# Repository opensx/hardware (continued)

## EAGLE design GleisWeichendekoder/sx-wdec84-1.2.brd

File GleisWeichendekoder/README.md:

# Weichendekoder für den direkten Anschluss ans Gleis 

Dies ist ein Weichendekoder zum direkten Einbau z.B. in das "C-Gleis", mehr dazu bei <a href="http://opensx.net/projekte/funktionsdekoder/gleis-wdec/"> Gleis-Weichendekoder auf opensx.net</a> .

<br />This work is licensed under a <a rel="license" href="http://creativecommons.org/licenses/by-sa/4.0/">Creative Commons Attribution-ShareAlike 4.0 International License</a>.

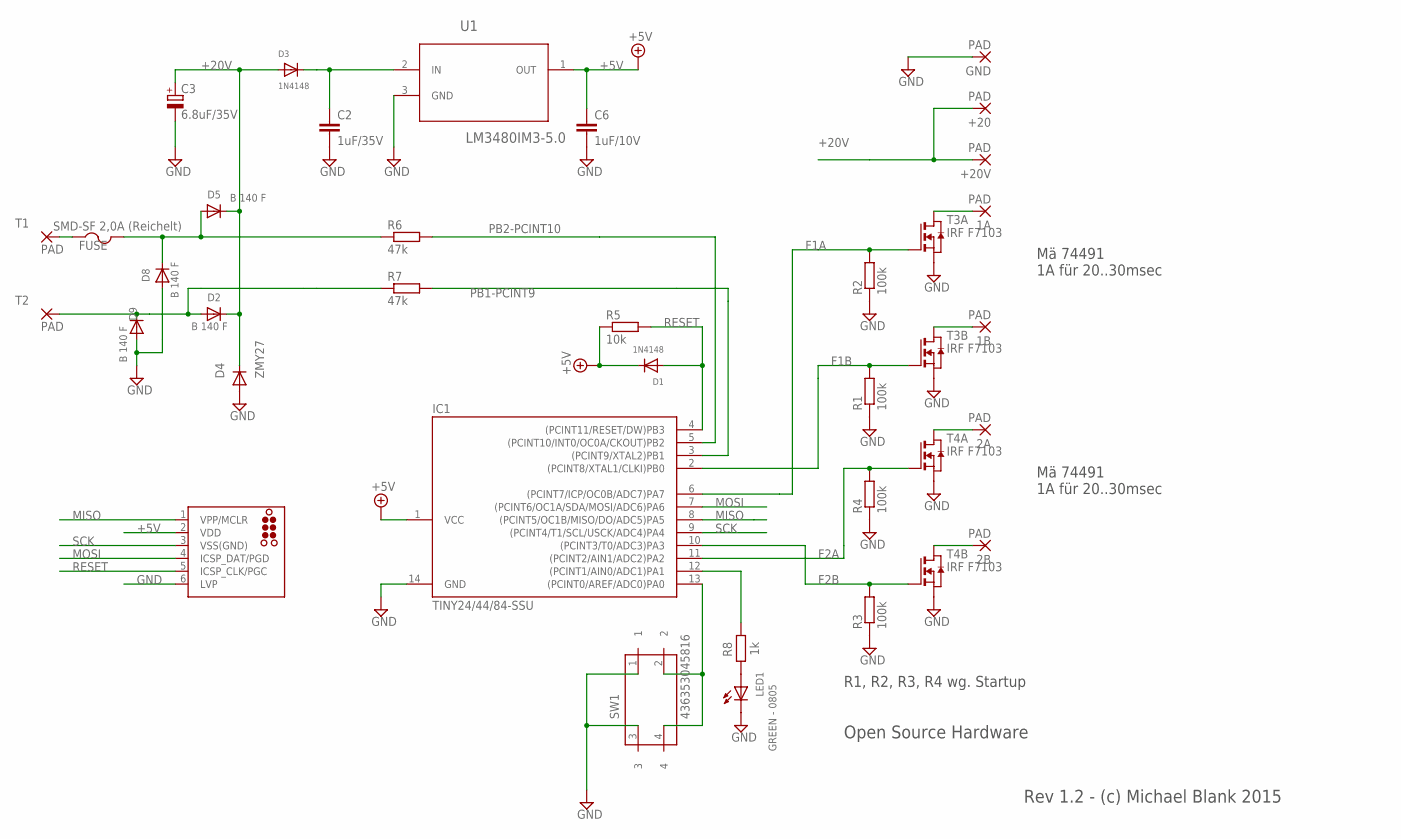
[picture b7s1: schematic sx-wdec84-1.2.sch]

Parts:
1A, 1B, 2A, 2B: PAD; SMD1,27-2,54
+20, +20V: PAD; SMD1,27-2,54
C2: 1uF/35V; C0805
C3: 6.8uF/35V; SMC_D
C6: 1uF/10V; C0805
D1, D3: 1N4148; SOD-323F
D2, D5, D8, D9: B 140 F; SMA-403D
D4: ZMY27; MELF-MLL41
FUSE: SMD-SF 2,0A (Reichelt); 1812
GND: PAD; SMD1,27-2,54
IC1: TINY24/44/84-SSU; SOIC14
J1: ISP; TC2030-MCP-NL
LED1: GREEN - 0805; LED-0805
R1, R2, R3, R4: 100k; R0805W
R5: 10k; R0805W
R6, R7: 47k; R0805W
R8: 1k; R0805W
SW1: 436353045816
T1, T2: PAD; SMD1,27-2,54
T3, T4: IRF F7103; SO8
U1: LM3480IM3-5.0; SOT95P263X110-3N

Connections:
+5V: C6.1, D1.C, IC1.1 (VCC), J1.2 (VDD), R5.1, U1.1 (OUT)
+20V: +20.1, +20V.1, C3.+, D2.C, D3.A, D4.C, D5.C
F1A: IC1.6 ((PCINT7/ICP/OC0B/ADC7)PA7), R2.2, T3.2 (G)
F1B: IC1.2 ((PCINT8/XTAL1/CLKI)PB0), R1.2, T3.4 (G)
F2A: IC1.11 ((PCINT2/AIN1/ADC2)PA2), R4.2, T4.2 (G)
F2B: IC1.10 ((PCINT3/T0/ADC3)PA3), R3.2, T4.4 (G)
GND: C2.2, C3.-, C6.2, D4.A, D8.A, D9.A, GND.1, IC1.14 (GND), J1.6 (LVP), LED1.C, R1.1, R2.1, R3.1, R4.1, SW1.1, SW1.3, T3.1 (S), T3.3 (S), T4.1 (S), T4.3 (S), U1.3 (GND)
MISO: IC1.8 ((PCINT5/OC1B/MISO/DO/ADC5)PA5), J1.1 (VPP/MCLR)
MOSI: IC1.7 ((PCINT6/OC1A/SDA/MOSI/ADC6)PA6), J1.4 (ICSP_DAT/PGD)
unnamed: 2B.1, T4.5 (D), T4.6 (D)
unnamed: 2A.1, T4.7 (D), T4.8 (D)
unnamed: FUSE.1, T1.1
unnamed: IC1.13 ((PCINT0/AREF/ADC0)PA0), SW1.2, SW1.4
unnamed: D5.A, D8.C, FUSE.2, R6.1
unnamed: C2.1, D3.C, U1.2 (IN)
unnamed: 1B.1, T3.5 (D), T3.6 (D)
unnamed: LED1.A, R8.2
unnamed: 1A.1, T3.7 (D), T3.8 (D)
unnamed: IC1.12 ((PCINT1/AIN0/ADC1)PA1), R8.1
PB1-PCINT9: IC1.3 ((PCINT9/XTAL2)PB1), R7.2
PB2-PCINT10: IC1.5 ((PCINT10/INT0/OC0A/CKOUT)PB2), R6.2
RESET: D1.A, IC1.4 ((PCINT11/RESET/DW)PB3), J1.5 (ICSP_CLK/PGC), R5.2
SCK: IC1.9 ((PCINT4/T1/SCL/USCK/ADC4)PA4), J1.3 (VSS(GND))
TR-L: D2.A, D9.C, R7.1, T2.1

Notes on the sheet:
Mä 74491 1A für 20..30msec
R1, R2, R3, R4 wg. Startup
Open Source Hardware
Rev 1.2 - (c) Michael Blank 2015

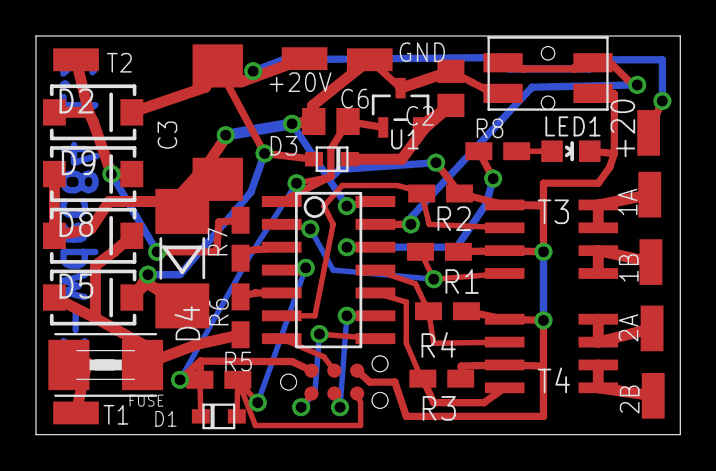
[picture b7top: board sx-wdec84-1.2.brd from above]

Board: 2 copper layers, 35.8 x 22.1 mm, 35 parts (0 on the bottom side), 24 nets.

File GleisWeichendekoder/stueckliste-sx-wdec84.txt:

Stueckliste

(sx-wdec84.brd at 13.12.15)


Part         Wert                Package            Bemerkung                Reichelt Best-Nr.

C2           1uF/35V             C0805              keram. C                 X7R-G0805 1,0/50 
C3           6.8uF/35V           SMC_D              Tantal-Elko              SMD TAN.6,8/35
C6           1uF/10V             C0805              keram. C                 X7R-G0805 1,0/16
D1, D3       1N4148              SOD-123 (falsch!)  Standard Diode           1N4148 WS
D2,D5,D8,D9  B140F               SMA-403D           Schottky-D. (40V, 1A)    B 140 F
D4           ZMY27               MELF-MLL41         Z-Diode                  SMD ZF 27
FUSE         SMD-SF 2,0A         1812               PTC                      SMD-SF 2,0A
IC1          ATTINY84-SSU        SOIC14             Atmel Proz.              ATTINY 84A-SSU
J1           ISP                 TC2030-MCP-NL                               (falls der Tiny84 in der schaltung progrmmiert 
                                                                             werden soll: TAG-CONNECT 6pin ISP)
LED1         GREEN               LED-0805                                    SMD-LED 0805 GN 
R1,R2,R3,R4  100k                R0805                                       SMD-0805 100K
R5           10k                 R0805                                       SMD-0805 100K
R6,R7        47k                 R0805                                       SMD-0805 100K
R8           1k                  R0805                                       SMD-0805 100K
S1           EVQP2202W           TACTILE_SWITCH_SMD                          (RS Components 756-1760 - oder Conrad 711761 - 62)
T3,T4        IRF F7103           SO8                Dual MosFET              IRF 7103
U1           LM3480IM3-5.0       SOT95P263X110-3N   5V Regler                (Conrad LM3480IM3-5.0/NOPB)

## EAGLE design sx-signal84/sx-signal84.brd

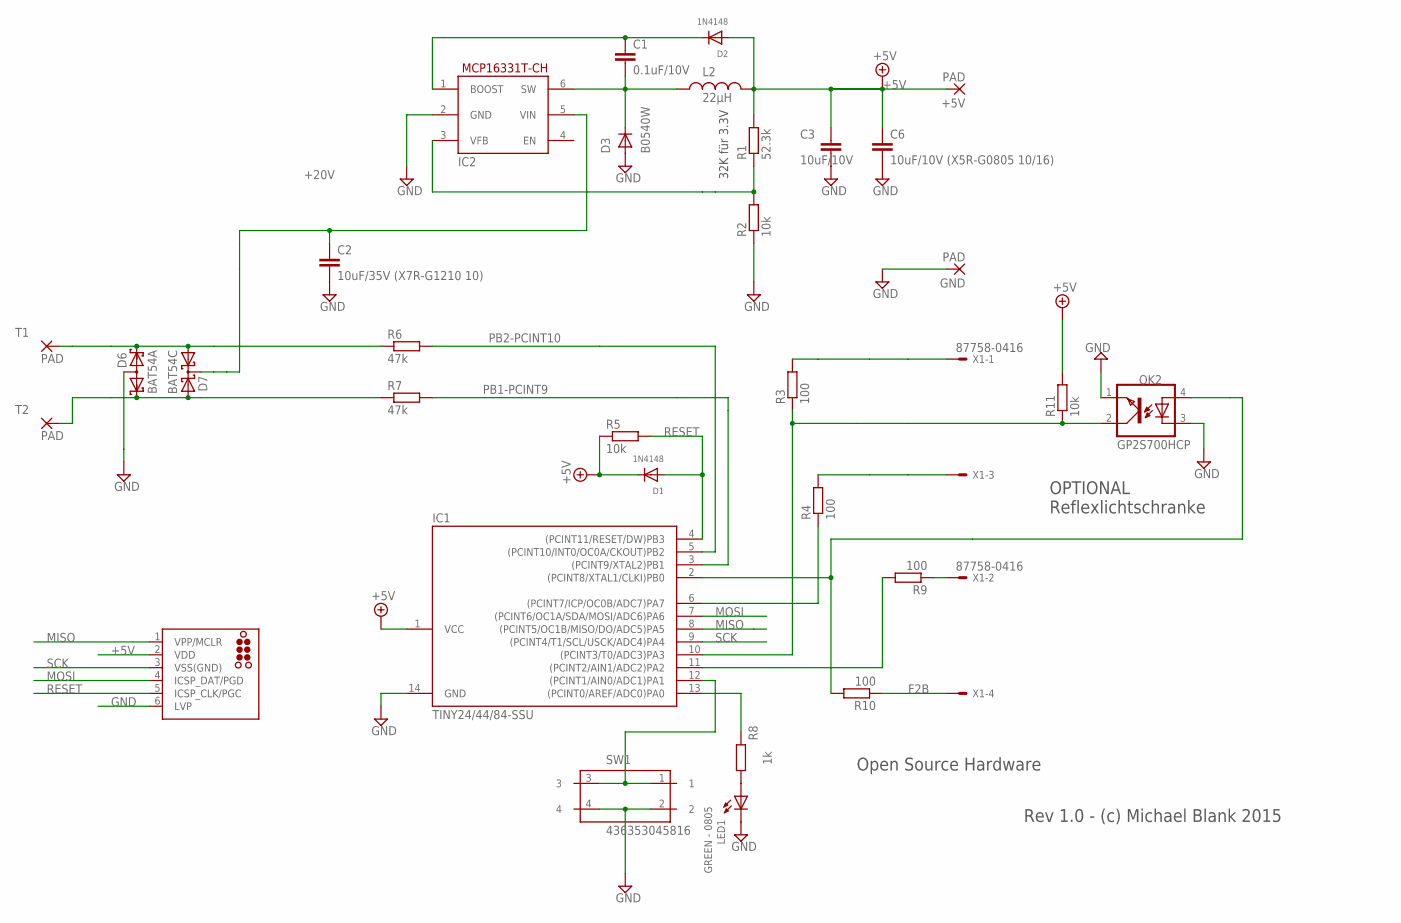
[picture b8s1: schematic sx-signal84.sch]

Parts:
+5V: PAD; SMD1,27-2,54
C1: 0.1uF/10V; C0805
C2: 10uF/35V (X7R-G1210 10); C1210
C3: 10uF/10V; C0805
C6: 10uF/10V (X5R-G0805 10/16); C0805
D1, D2: 1N4148; SOD-323F
D3: B0540W; SOD123
D6: BAT54A; SOT23
D7: BAT54C; SOT23
GND: PAD; SMD1,27-2,54
IC1: TINY24/44/84-SSU; SOIC14
IC2: MCP16331; SOT23-6
J1: ISP; TC2030-MCP-NL
L2: 22µH; B82462G
LED1: GREEN - 0805; LED-0805
OK2: GP2S700HCP; SMD4-REFL
R1: 52.3k; R0805W
R2, R5, R11: 10k; R0805W
R3, R4, R9, R10: 100; R0805W
R6, R7: 47k; R0805W
R8: 1k; R0805W
SW1: 436353045816
T1, T2: PAD; SMD1,27-2,54
X1: 87758-0416

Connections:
+5V: +5V.1, C3.1, C6.1, D1.C, D2.A, IC1.1 (VCC), J1.2 (VDD), L2.P$2 (2), R1.2, R5.1, R11.2
+20V: C2.1, D7.3 (CC), IC2.5 (VIN)
F1A: IC1.10 ((PCINT3/T0/ADC3)PA3), OK2.2 (COL), R3.1, R11.1
F1B: IC1.2 ((PCINT8/XTAL1/CLKI)PB0), OK2.4 (A), R10.2
F2B: R10.1, X1.4
GND: C2.2, C3.2, C6.2, D3.A, D6.3 (AA), GND.1, IC1.14 (GND), IC2.2 (GND), J1.6 (LVP), LED1.C, OK2.1 (EMIT), OK2.3 (C), R2.1, SW1.2, SW1.4
MISO: IC1.8 ((PCINT5/OC1B/MISO/DO/ADC5)PA5), J1.1 (VPP/MCLR)
MOSI: IC1.7 ((PCINT6/OC1A/SDA/MOSI/ADC6)PA6), J1.4 (ICSP_DAT/PGD)
unnamed: IC2.3 (VFB), R1.1, R2.2
unnamed: IC1.13 ((PCINT0/AREF/ADC0)PA0), R8.1
unnamed: IC1.12 ((PCINT1/AIN0/ADC1)PA1), SW1.1, SW1.3
unnamed: IC1.6 ((PCINT7/ICP/OC0B/ADC7)PA7), R4.1
unnamed: R9.1, X1.2
unnamed: C1.2, D3.C, IC2.6 (SW), L2.P$1 (1)
unnamed: C1.1, D2.C, IC2.1 (BOOST)
unnamed: LED1.A, R8.2
unnamed: IC1.11 ((PCINT2/AIN1/ADC2)PA2), R9.2
unnamed: D6.2 (K2), D7.1 (A1), R6.1, T1.1
unnamed: R3.2, X1.1
unnamed: R4.2, X1.3
PB1-PCINT9: IC1.3 ((PCINT9/XTAL2)PB1), R7.2
PB2-PCINT10: IC1.5 ((PCINT10/INT0/OC0A/CKOUT)PB2), R6.2
RESET: D1.A, IC1.4 ((PCINT11/RESET/DW)PB3), J1.5 (ICSP_CLK/PGC), R5.2
SCK: IC1.9 ((PCINT4/T1/SCL/USCK/ADC4)PA4), J1.3 (VSS(GND))
TR-L1: D6.1 (K1), D7.2 (A2), R7.1, T2.1

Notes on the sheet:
Open Source Hardware
Rev 1.0 - (c) Michael Blank 2015
OPTIONAL Reflexlichtschranke
32K für 3.3V

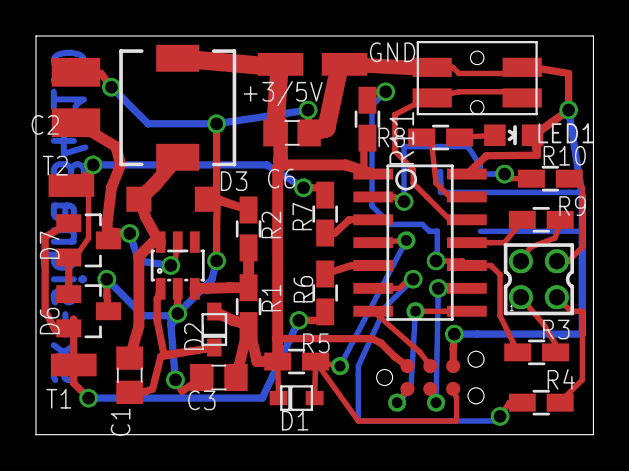
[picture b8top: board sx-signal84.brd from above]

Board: 2 copper layers, 31.0 x 22.1 mm, 32 parts (1 on the bottom side), 25 nets.

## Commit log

2015-12-13 removed cern..
2015-12-13 added linkt to cc licence
2015-12-13 Basisplatine und SX-RJ-Verteiler hinzugefügt
2015-12-13 corr readme
2015-12-13 pdf added
2015-12-13 readme corr.
2015-12-13 foto hinzu
2015-12-13 readme corr
2015-12-14 Gleis Weichendekoder hinzugefügt
2015-12-14 bild sx-wdec84 hinzu
2015-12-23 gleisdekoder hinzugefügt
2015-12-23 Gleis Signaldekoder
2016-08-26 Basisplatine-2.0 hinzugefügt
2016-08-26 fotos hinzu
2016-08-26 Belegtmelder 1.0 hinzu
2016-09-06 begin stueckliste
2016-09-16 Anleitung f. Basispl. für belegtmelder(5Volt)
2016-11-20 sx-wdec1-2313 files hinzugefügt.
2016-11-20 readme ergänzt
2016-11-20 eagle files f. sx-wdec1-2313
2016-11-20 readme korr.
2016-11-26 partlist ergänzt
2016-11-28 Create RT-Weiche-Signal
2016-11-28 neue Platine rt-weiche-signal
2016-11-28 typo README corr.
2016-12-01 RT-Weiche-Signal hardware
2016-12-17 template für fundec45
2016-12-17 sx-fundec45 hinzugefügt
2016-12-17 corr. readme von rt-weiche-signal
2016-12-17 erste Version parts lists
2016-12-24 schematics und brd for Arduino lok-dec-328 hinzu
2017-11-02 added gerber files
2017-11-06 SX-Belegtmelder Gerber Files (.zip)
2017-11-06 added ref to gerber files .zip
2017-11-07 added RT-Weiche8
2017-11-07 added pcb foto
2017-11-07 clarified README
2018-08-29 added eagle files
2018-08-29 Update README.md
    pdf for rev.3 of hardware
2018-10-17 new HW SX-Belegt2.10
2018-10-17 eagle files to SX-Belegt-2.10
2018-11-15 SX-Belegt2.10 Aufsetzplatine und SX-WDEC_SMD-4313
